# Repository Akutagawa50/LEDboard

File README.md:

# LEDboard
## 概要
LEDを5つアノードコモンで接続した基板

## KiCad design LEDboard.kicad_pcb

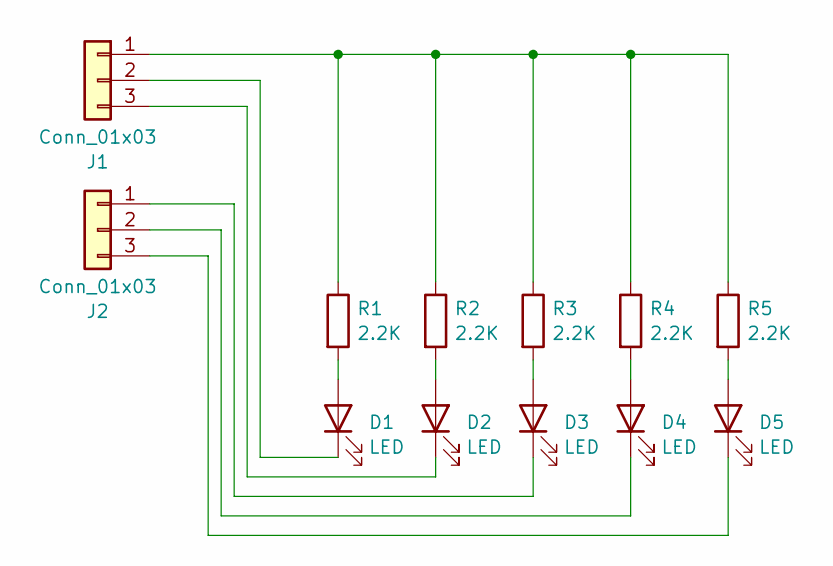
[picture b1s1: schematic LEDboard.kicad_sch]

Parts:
D1, D2, D3, D4, D5: LED; LED_D3.0mm
J1, J2: Conn_01x03; EuroBlock_receptacle_2.54_3p
R1, R2, R3, R4, R5: 2.2K; R_Axial_DIN0204_L3.6mm_D1.6mm_P7.62mm_Horizontal

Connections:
unnamed: D1.2 (A), R1.2
unnamed: D1.1 (K), J1.2
unnamed: D2.2 (A), R2.2
unnamed: D2.1 (K), J1.3
unnamed: D3.2 (A), R3.2
unnamed: D3.1 (K), J2.1
unnamed: D4.2 (A), R4.2
unnamed: D4.1 (K), J2.2
unnamed: D5.2 (A), R5.2
unnamed: D5.1 (K), J2.3
unnamed: J1.1, R1.1, R2.1, R3.1, R4.1, R5.1

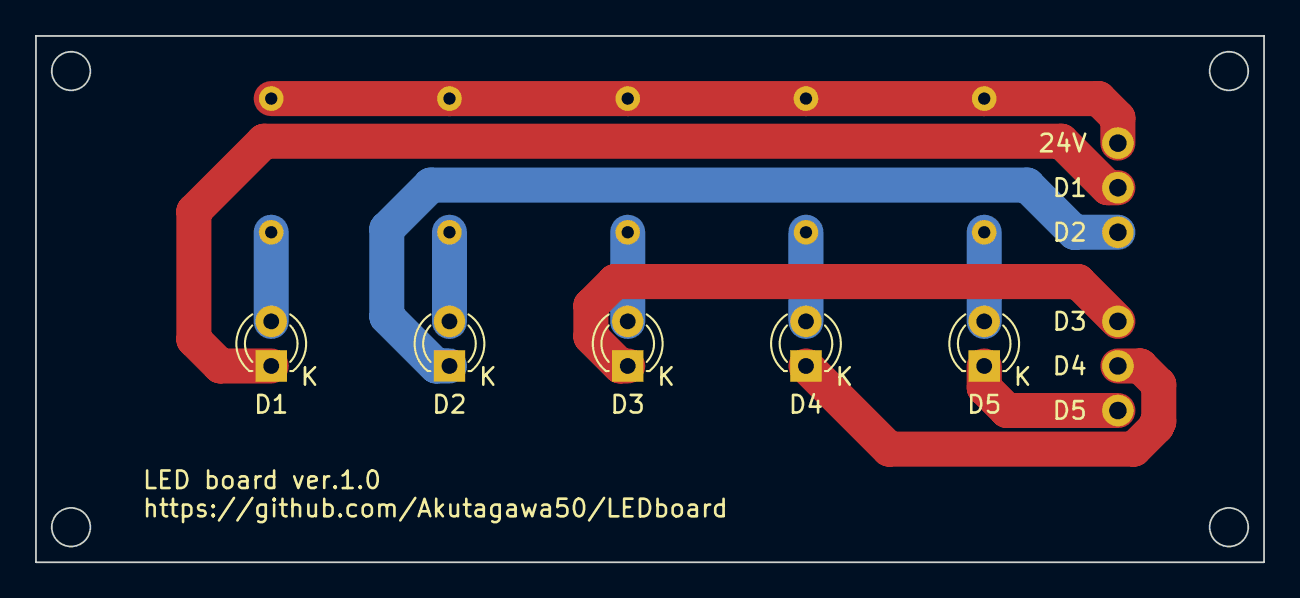
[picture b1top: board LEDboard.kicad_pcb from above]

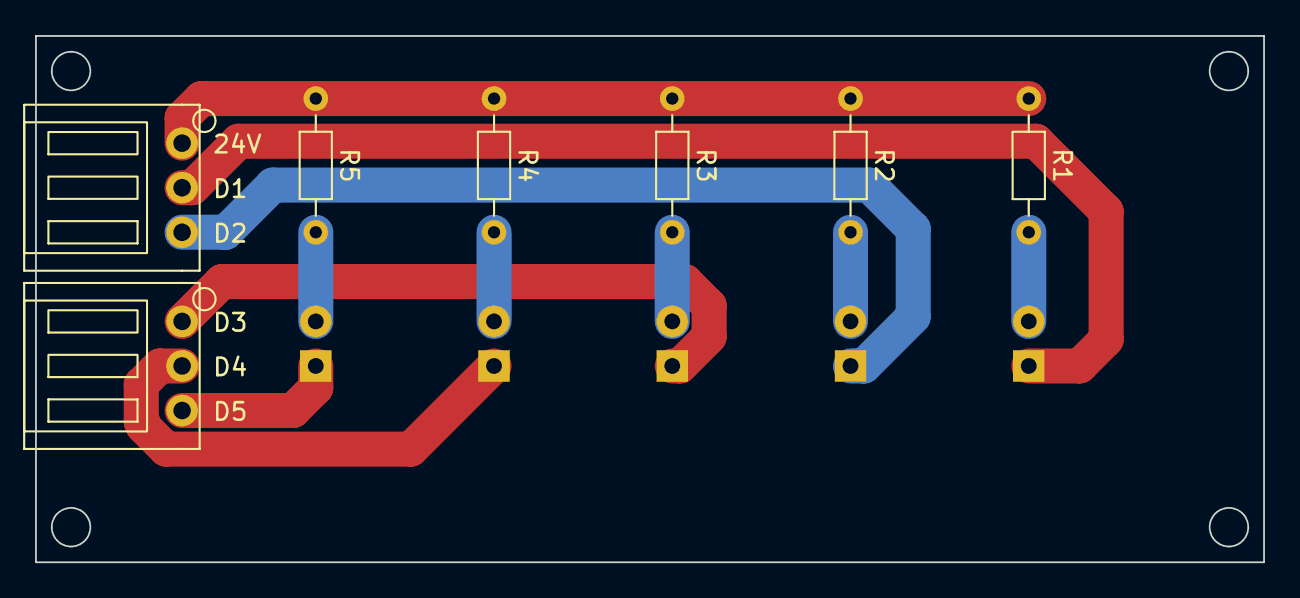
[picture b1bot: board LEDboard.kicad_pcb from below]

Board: 2 copper layers, 70.0 x 30.0 mm, 12 parts (7 on the bottom side), 11 nets.

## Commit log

2024-08-10 ファイルを新規作成
2024-08-10 Create LICENSE
2024-10-03 KiCad8.0にアップデート
2024-10-03 add new file
2024-10-03 @echo off を追加
